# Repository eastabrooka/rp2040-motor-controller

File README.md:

# rp2040-motor-controller

## Note: This is a from the upstream Twisted-Fields/rp2040-motor-controller repo.

### Intro / First Level Why ? 

Well, I find this very interesting / funny. 

The previous EMFcamps I have attended, I have always tried to "Make something that moved humans". 

One of them was a giant DC Wheelchair powered Creeper, 

One of them was Wheelchair Gokart. 

The most recent was a Brushless Hoverboard Kart / Trike. 

In all of these cases, the motor controllers have let me down. 

So this is my current working directory for making my own "Flavour" of Brushless Motor Controller.

### Second Level Why ? 

Well, Brushless motor controllers are Expensive. Theres things like the VESC, ODrive and the cheap red 300W Aliexpress controllers. 

The Ali Express controlers I have had go bang. 

The ODrive controllers are *Way* too expensive, and now, sadly, closed source. (Little bit salty about that)

Honestly, the smart move would probably be : Just buy Aliexpress cloned odrive boards. 
But then I dont learn anything. 

Anyway, All the changes here are under the same CERN Permissive as upstream. 

*Our dream is that you will fab your own boards, make changes, and share your work - giving this design life beyond our efforts.* - So I hope this plays nice with that. 

More info to come when I start hacking about a bit more.

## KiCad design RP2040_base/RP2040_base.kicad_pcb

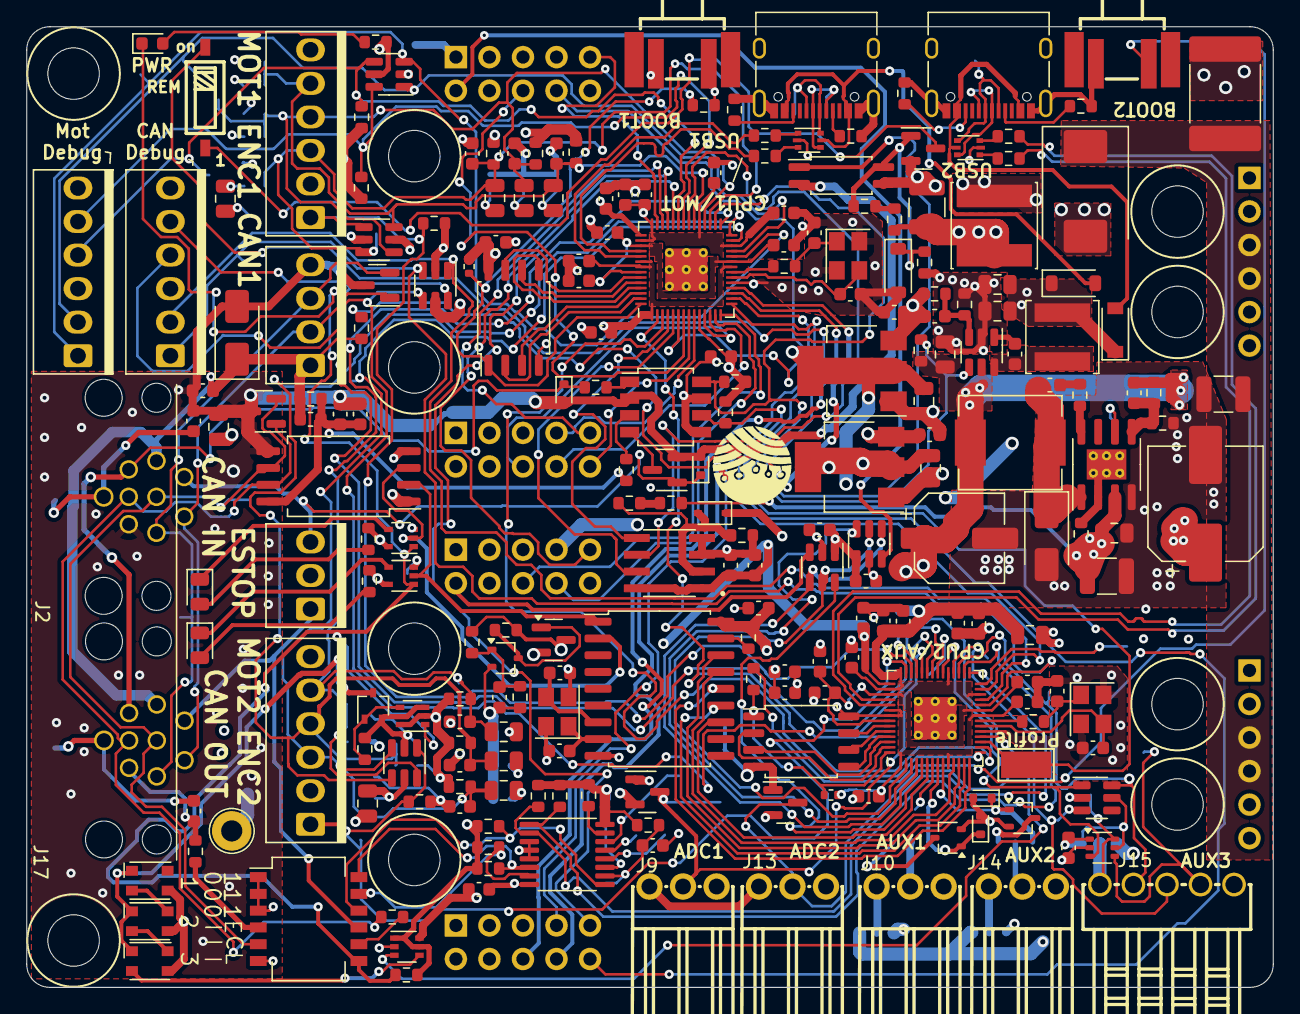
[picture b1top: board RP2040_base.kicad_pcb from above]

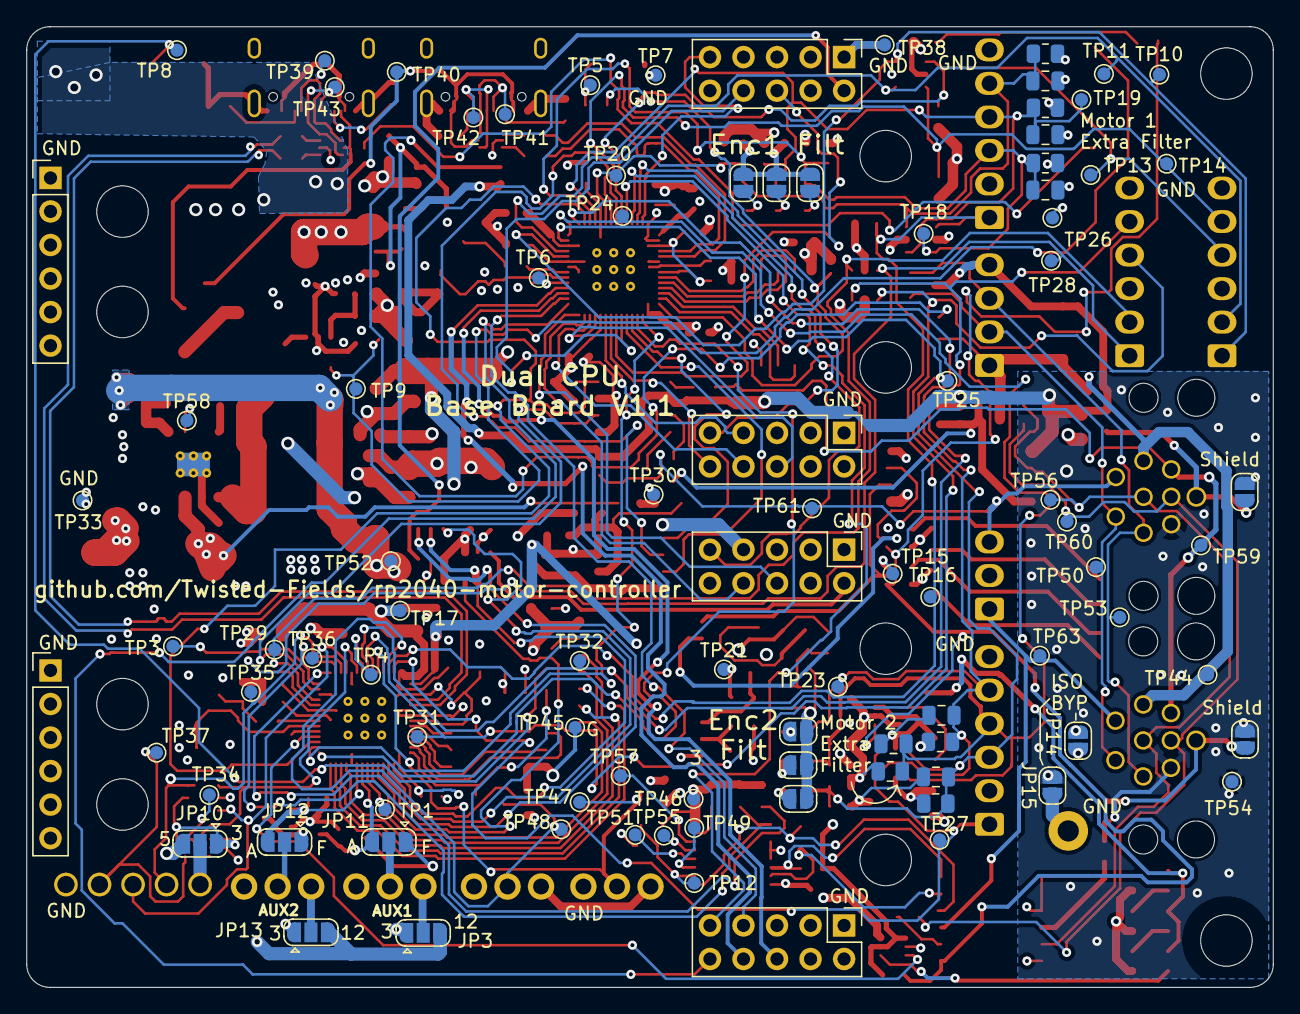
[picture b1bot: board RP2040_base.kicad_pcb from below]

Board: 4 copper layers, 94.4 x 72.8 mm, 315 parts (87 on the bottom side), 186 nets.

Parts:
C1, C8: 4.7uF 35V; C_0603_1608Metric
C2, C3, C111: 4.7uF 100V; C_1210_3225Metric
C4, C21, C22, C30, C31, C33, C36, C37, C38, C39, C40, C41, C43, C44, C45, C46, C47, C48, C49, C50, C51, C52, C55, C56, C67, C114, C119: 100n; C_0603_1608Metric
C5, C6, C7, C9, C10, C11: C_0805_2012Metric
C12, C13, C24, C29, C86, C110: 10u; C_0805_2012Metric
C14: 10uF 25v; C_0603_1608Metric
C15: 2.2u; C_0603_1608Metric
C18, C20, C32, C34, C35, C53, C54, C121, C122, C123, C124: 1u; C_0603_1608Metric
C19, C27, C28, C42: 20p; C_0603_1608Metric
C23, C60, C61, C62, C63, C64, C113: 47p; C_0603_1608Metric
C57, C58: 18p; C_0603_1608Metric
C87, C88, C89, C90, C91, C92: 22nF; C_0805_2012Metric
C94, C96: 22uF 25V; C_0805_2012Metric
C95: 47uF 10v; C_0805_2012Metric
C97: 22pF; C_0603_1608Metric
C98: 22nF; C_0603_1608Metric
C112: 100nF 100V; C_0805_2012Metric
C115: 220uF 25V; CP_Elec_6.3x7.7
C120: 47uF 63V solid; CP_Elec_8x10.5
D1, D40: ESDCAN24-2BLY; SOT-23
D3: TVS 5V; D_SMA
D4: SMAJ51A; D_SMC
D27: SS310; D_SMA
D28, D29, D30, D32: TVS 3.3V; D_SOD-523
D31: 1N4148WS; D_SOD-323
D33, D34, D35: WS2812B; LED_WS2812_3528_3.5x2.8mm_P1.5mm
D36, D44: BAT54S; SOT-23
D37, D43: B5819W SL; D_SOD-123
D38: LED_GREEN; LED_0805_2012Metric
D39: LED_YELLOW; LED_0805_2012Metric
D41: LED_RED; LED_0603_1608Metric
D45: 10V Zener; D_SOD-123
F1: 60V 1.5A hold polyfuse; Fuse_2920_7451Metric
FB2: 1.6Ω ±25% 1kΩ@100MHz; L_0603_1608Metric
H3, H4: MountingHole; MountingHole_3.9mm_Plastite_#6
J1: CPU1 USB; USB_C_Receptacle_XKB_U262-16XN-4BVC11
J2: CAN Input; M12A-08PFFR
J3: Encoder 1; Ckmtw-W-2510S06P_1x06_P2.54mm_Vertical
J4: Encoder 2; Ckmtw-W-2510S06P_1x06_P2.54mm_Vertical
J5, J12: Conn_01x06; Ckmtw-W-2510S06P_1x06_P2.54mm_Vertical
J6: CPU2 USB; USB_C_Receptacle_XKB_U262-16XN-4BVC11
J8: Estop Conn; BOOMELE-2510-3A_1x03_P2.54mm_Vertical
J9: ADC AUX 1; CONN-TH_3P-P2.54_HCTL_HC-2510-3AW
J10: AUX GPIO 1; CONN-TH_3P-P2.54_HCTL_HC-2510-3AW
J11: CAN2 PLUG; PINREX-744-81-04TW00 _1x04_P2.54mm_Vertical
J13: ADC AUX 2; CONN-TH_3P-P2.54_HCTL_HC-2510-3AW
J14: AUX GPIO 2; CONN-TH_3P-P2.54_HCTL_HC-2510-3AW
J15: AUX Encoder; CONN-TH_5P-P2.54_HCTL_HC-2510-5AW
J17: CAN Output; M12A-08PFFR
JP1, JP2, JP4, JP5, JP6, JP7, JP8, JP9, JP14, JP15: SolderJumper_2_Open; SolderJumper-2_P1.3mm_Open_RoundedPad1.0x1.5mm
JP3, JP10, JP11, JP12, JP13: SolderJumper_3_Open; SolderJumper-3_P1.3mm_Open_RoundedPad1.0x1.5mm
L1: 68uH 1A; L_Sunlord_SWPA6045S
L2: 10uH; L_Sunlord_SWPA5040S
L3: 47uH; L_Chilisin_BMRB00060612
Q1, Q2, Q11: AO7400-VB; SOT-323_SC-70
Q3: AO7401; SOT-23
Q4: LBSS139WT1G; SOT-323_SC-70
Q7, Q8: Q_NMOS_GSD; SOT-23
R1, R3, R4, R5, R6, R7: R_0805_2012Metric
R2, R23, R64: 50k 0.1%; R_0603_1608Metric
R8, R11, R12, R13, R14, R17, R18, R19, R53, R54, R55, R56, R57, R58, R72, R74, R79, R137, R138: 10k; R_0603_1608Metric
R9, R48, R75, R100: 120R; R_0603_1608Metric
R10: 510R; R_0603_1608Metric
R15: 110k 0.1%; R_0603_1608Metric
R16: 15k 0.1%; R_0603_1608Metric
R20, R21: 47k; R_0603_1608Metric
R22: 500k; R_0603_1608Metric
R40, R43, R44, R46, R49, R62, R63, R76: 5.1k; R_0603_1608Metric
R41, R47, R52, R66: 1.1k; R_0603_1608Metric
R42, R51: DNS; R_0402_1005Metric
R60, R61, R67, R70, R71: 27R; R_0603_1608Metric
R65: 5.1k 0.1%; R_0603_1608Metric
R68: 56R; R_0603_1608Metric
R77: 82R; R_0603_1608Metric
R95: 30mΩ 5%; R_0603_1608Metric
R96: 300k; R_0603_1608Metric
R97: 21.5k; R_0603_1608Metric
R98: 10Ω; R_0603_1608Metric
R99: 10.2R; R_0603_1608Metric
R103, R106: 100k; R_0603_1608Metric
SW1, SW5: KT11B2SAM34LFS; KEY-SMD_KT11B2SAM34LFS
SW3: CONFIG SWITCH; SW_DIP_SPSTx06_Slide_KingTek_DSHP06TS_W7.62mm_P1.27mm
SW4: SW_DIP_x01; SW-SMD_DSHP01TSGER
TP1, TP3, TP4, TP5, TP6, TP7, TP8, TP9, TP10, TP11, TP12, TP13, TP14, TP15, TP16, TP17, TP18, TP19, TP20, TP21, TP23, TP24, TP25, TP26, TP27, TP28, TP29, TP30, TP31, TP32, TP33, TP34, TP35, TP36, TP37, TP38, TP39, TP40, TP41, TP42, TP43, TP44, TP45, TP46, TP47, TP48, TP49, TP50, TP51, TP52, TP53, TP54, TP55, TP56, TP57, TP58, TP59, TP60, TP61, TP63: TestPoint; TestPoint_Pad_D1.0mm
TP2: TestPoint; TestPoint_Loop_D2.60mm_Drill1.6mm_Beaded
TP22: TestPoint; TestPoint_Keystone_5019_Minature
U1, U2: driver_module
U3, U29, U30, U31, U43: USBLC6-4SC6; SOT-23-6
U4, U10: TXS0101DCKR; SOT-363_SC-70-6
U6, U23, U25: SN74LVC1G07QDCKTQ1; SOT-353_SC-70-5
U9, U26: ADC081S021CISD/NOPB; SOT-23-6
U11, U32: TLV1117LV33DCYR; SOT-223-3_TabPin2
U12, U13: W25Q128JVSIQ; SOIC-8_5.23x5.23mm_P1.27mm
U15, U19: RP2040; RP2040-QFN-56
U16: SOP-4_4.4x2.6mm_P1.27mm
U17: CA-IS3052G; SOIC-8_7.5x5.85mm_P1.27mm
U18: MCP2515-xSO; SOIC-18W_7.5x11.6mm_P1.27mm
U22: ADS7822U; SOIC127P599X175-8N
U24: MT2492; SOT-23-6
U27, U28: USBLC6-2P6; SOT-666
U33: TX4139; SOIC-8-1EP_3.9x4.9mm_P1.27mm_EP2.29x3mm_ThermalVias
U34: LTV-208; SSOP-8_3.91x5.84x3.18mm_P1.27mm
U35: PCA9557PWR; TSSOP-16_4.4x5mm_P0.65mm
Y1, Y2: 12MHz; Crystal_SMD_3225-4Pin_3.2x2.5mm
Y3: 16MHz; Crystal_SMD_3225-4Pin_3.2x2.5mm

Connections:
+1V1: C30.1, C31.1, C32.1, U15.23 (DVDD), U15.45 (VREG_VOUT), U15.50 (DVDD)
+3.3VA: C18.2, C20.2, C22.1, C24.1, C35.2, C41.1, C52.1, D31.1 (K), D36.2 (K), D44.2 (K), J9.1, J13.1, U1.7 (+3V3), U2.7 (+3V3), U9.1 (VA), U11.2 (VO), U15.43 (ADC_AVDD), U19.43 (ADC_AVDD), U22.1 (VREF), U22.8 (+VCC), U26.1 (VA)
+3V3: C4.1, C12.2, C13.2, C21.1, C29.1, C33.1, C34.1, C36.1, C37.1, C38.1, C39.1, C40.1, C43.1, C46.1, C47.1, C48.1, C49.1, C50.1, C51.1, C54.1, C56.2, C67.1, C110.1, J3.2, J4.2, J5.3, J12.3, JP3.1 (A), JP10.1 (A), JP13.1 (A), R1.1, R3.1, R4.1, R5.1, R6.1, R7.1, R11.1, R12.1, R13.1, R17.1, R18.1, R19.1, R23.1, R42.1, R49.1, R51.1, R53.1, R54.1, R55.1, R56.1, R57.1, R58.1, R62.1, R63.2, R67.1, R68.1, R72.2, R76.1, R77.1, R137.2, TP17.1, TP26.1, TP30.1, TP46.1, U3.5 (VBUS), U4.1 (VCCA), U4.5 (OE), U6.5 (VCC), U10.1 (VCCA), U10.5 (OE), U12.8 (VCC), U13.8 (VCC), U15.1 (IOVDD), U15.10 (IOVDD), U15.22 (IOVDD), U15.26 (RUN), U15.33 (IOVDD), U15.42 (IOVDD), U15.44 (VREG_IN), U15.48 (USB_VDD), U15.49 (IOVDD), U17.1 (VCC1), U18.18 (VDD), U19.1 (IOVDD), U19.10 (IOVDD), U19.22 (IOVDD), U19.26 (RUN), U19.33 (IOVDD), U19.42 (IOVDD), U19.44 (VREG_IN), U19.48 (USB_VDD), U19.49 (IOVDD), U23.5 (VCC), U25.2 (A), U25.5 (VCC), U29.5 (VBUS), U30.5 (VBUS), U31.5 (VBUS), U32.2 (VO), U35.16 (VDD), U43.5 (VBUS)
+5V: C95.2, C96.2, C97.1, C119.1, C121.1, C122.1, D33.3 (VDD), D34.3 (VDD), D35.3 (VDD), D37.1 (K), D43.1 (K), JP10.3 (B), JP14.1 (A), L2.2, R15.2, U10.6 (VCCB), U11.3 (VI), U32.3 (VI)
+5V_ISO: C8.2, D3.1 (A1), FB2.2, J2.7, J11.1, J17.7, JP14.2 (B), R99.2, R100.1, TP44.1
+5V_ISO_FILT: C1.2, C55.2, FB2.1, R48.1, R99.1, U17.8 (VCC2)
+12V: C94.1, C113.1, C115.1, JP3.3 (B), JP13.3 (B), L3.2, Q3.3 (D), R20.2, R21.2, R96.2, R106.1, TP52.1, U24.5 (IN)
/1V1_2: C44.1, C45.1, C53.1, U19.23 (DVDD), U19.45 (VREG_VOUT), U19.50 (DVDD)
/5V_EN: R106.2, SW4.2, TP9.1, U24.4 (EN)
/12V_switched: Q3.2 (S), U1.5 (+12V), U2.5 (+12V)
/ADC_AUX1: D44.3 (COM), J9.2, TP47.1, U19.38 (GPIO26_ADC0)
/ADC_AUX2: D36.3 (COM), J13.2, TP48.1, U19.39 (GPIO27_ADC1)
/ADC_CLK: U9.4 (SCLK), U19.4 (GPIO2), U26.4 (SCLK)
/ADC_CS1: U9.6 (~CS), U19.3 (GPIO1)
/ADC_CS2: U19.5 (GPIO3), U26.6 (~CS)
/ADC_DATA: U9.5 (SDATA), U19.2 (GPIO0), U26.5 (SDATA)
/AUX1: D30.1 (A1), JP11.3 (B), Q1.1 (G), U19.8 (GPIO6)
/AUX2: D29.1 (A1), JP12.3 (B), Q2.1 (G), U19.9 (GPIO7)
/AUX3_CSn: J15.3, TP36.1, U19.32 (GPIO21), U31.3 (I/O2)
/AUX3_RX: J15.2, TP35.1, U19.31 (GPIO20), U31.6 (I/O4)
/AUX3_SCK: U4.3 (A), U19.34 (GPIO22), U31.1 (I/O1)
/AUX3_SCK_SHIFTED: J15.4, TP37.1, U4.4 (B)
/AUXV: J15.1, JP10.2 (C), TP34.1, U4.6 (VCCB)
/BS: R98.1, U33.8 (BS)
/Bridge_TH_1: U1.2 (Thermistor), U9.3 (VIN)
/Bridge_TH_2: U2.2 (Thermistor), U26.3 (VIN)
/CAN0_N: D1.2 (K), J2.8, J17.8, SW3.5, TP56.1, U17.6 (CANL)
/CAN0_P: D1.1 (K), J2.5, J17.5, R9.1, TP60.1, U17.7 (CANH)
/CAN1_N: D40.2 (K), J2.3, J11.3, J17.3, TP53.1
/CAN1_P: D40.1 (K), J2.2, J11.2, J17.2, TP50.1
/CANH0_P_JP: R9.2, SW3.8
/ENC1_CS: C7.2, C61.2, C88.1, J3.4, R3.2, R56.2, TP19.1, U15.32 (GPIO21), U29.4 (I/O3)
/ENC1_RX: C6.2, C62.2, C87.2, J3.3, R4.2, R58.2, TP18.1, U15.31 (GPIO20), U29.3 (I/O2)
/ENC1_SCK: C5.2, C60.2, C89.1, J3.5, R1.2, R54.2, TP20.1, U15.34 (GPIO22), U29.6 (I/O4)
/ENC2_CS: C11.2, C63.2, C91.2, J4.4, R6.2, R55.2, TP24.1, U15.28 (GPIO17), U30.4 (I/O3)
/ENC2_RX: C9.2, C64.2, C90.2, J4.3, R5.2, R57.2, TP25.1, U15.27 (GPIO16), U30.3 (I/O2)
/ENC2_SCK: C10.2, C23.2, C92.2, J4.5, R7.2, R53.2, TP23.1, U15.29 (GPIO18), U30.6 (I/O4)
/ESTOP: R76.2, TP22.1, U15.30 (GPIO19), U19.17 (GPIO14), U34.8
/ESTOP_SQUARE: D28.1 (A1), J2.6, J17.6, R75.1, TP59.1
/ESTOP_SWITCH_IN: D32.1 (A1), J2.1, J8.3, Q7.1 (G), TP61.1
/ESTOP_SWITCH_OUT: J8.1, J17.1, SW3.9, TP63.1
/ESTOP_SWITCH_STATUS: R49.2, U19.27 (GPIO16), U34.6
/FB: C113.2, R96.1, R97.2, U33.5 (FB)
/GPIO0: U15.2 (GPIO0), U19.16 (GPIO13)
/GPIO1: U15.3 (GPIO1), U19.15 (GPIO12)
/GPIO5_2: TP1.1, U19.7 (GPIO5)
/GPIO17_2: TP3.1, U19.28 (GPIO17)
/GPIO23: U15.35 (GPIO23), U22.6 (DOUT)
/GPIO23_2: TP4.1, U19.35 (GPIO23)
/GPIO24: J5.5, R62.2, TP14.1, U15.36 (GPIO24), U43.6 (I/O4)
/GPIO25: J5.4, R63.1, TP13.1, U15.37 (GPIO25), U43.4 (I/O3)
/ID1: R13.2, SW3.12, U35.6 (IO0)
/ID2: R12.2, SW3.11, U35.7 (IO1)
/ID3: R11.2, SW3.10, U35.9 (IO2)
/LED: U10.3 (A), U19.18 (GPIO15)
/QSPI_SCLK: U12.6 (CLK), U15.52 (QSPI_SCLK)
/QSPI_SCLK_2: U13.6 (CLK), U19.52 (QSPI_SCLK)
/QSPI_SD0: U12.5 (DI(IO0)), U15.53 (QSPI_SD0)
/QSPI_SD0_2: U13.5 (DI(IO0)), U19.53 (QSPI_SD0)
/QSPI_SD1: U12.2 (DO(IO1)), U15.55 (QSPI_SD1)
/QSPI_SD1_2: U13.2 (DO(IO1)), U19.55 (QSPI_SD1)
/QSPI_SD2: U12.3 (IO2), U15.54 (QSPI_SD2)
/QSPI_SD2_2: U13.3 (IO2), U19.54 (QSPI_SD2)
/QSPI_SD3: U12.7 (IO3), U15.51 (QSPI_SD3)
/QSPI_SD3_2: U13.7 (IO3), U19.51 (QSPI_SD3)
/QSPI_SS: R41.1, R42.2, U12.1 (~CS), U15.56 (QSPI_SS)
/QSPI_SS_2: R51.2, R66.1, U13.1 (~CS), U19.56 (QSPI_SS)
/RXD: U17.3 (RXD), U18.2 (RXCAN), U23.2 (A)
/RXI_2: J12.4, TP31.1, U3.4 (I/O3), U19.37 (GPIO25)
/SCL1: R18.2, U19.30 (GPIO19), U35.1 (SCL)
/SDA1: R19.2, U19.29 (GPIO18), U35.2 (SDA)
/SPI1_CSn_2: U18.16 (~CS), U19.12 (GPIO9)
/SPI1_INT: U18.12 (~INT), U19.6 (GPIO4)
/SPI1_RX_2: U18.15 (SO), U19.11 (GPIO8)
/SPI1_SCK_2: U18.13 (SCK), U19.13 (GPIO10)
/SPI1_TX_2: U18.14 (SI), U19.14 (GPIO11)
/SW: C114.1, D27.1 (K), L3.1, U33.1 (SW)
/SWCLK: J5.1, TP10.1, U15.24 (SWCLK), U43.3 (I/O2)
/SWCLK_2: J12.1, TP28.1, U3.3 (I/O2), U19.24 (SWCLK)
/SWD: J5.2, TP11.1, U15.25 (SWD), U43.1 (I/O1)
/SWD_2: J12.2, TP29.1, U3.1 (I/O1), U19.25 (SWD)
/TH_MOTOR1: J3.1, R74.1, TP16.1, U19.40 (GPIO28_ADC2), U29.1 (I/O1)
/TH_MOTOR2: J4.1, R79.1, TP27.1, U19.41 (GPIO29_ADC3), U30.1 (I/O1)
/TXD: U6.2 (A), U17.2 (TXD), U18.1 (TXCAN)
/TXO_2: J12.5, TP32.1, U3.6 (I/O4), U19.36 (GPIO24)
/USB_D+: J1.A6 (D+), J1.B6 (D+), TP41.1, U27.6 (I/O1)
/USB_D-: J1.A7 (D-), J1.B7 (D-), TP42.1, U27.4 (I/O2)
/USB_DN: R61.2, U15.46 (USB_DM)
/USB_DN_2: R71.2, U19.46 (USB_DM)
/USB_DP: R60.2, U15.47 (USB_DP)
/USB_DP_2: R70.2, U19.47 (USB_DP)
/USB_D_2+: J6.A6 (D+), J6.B6 (D+), TP43.1, U28.6 (I/O1)
/USB_D_2-: J6.A7 (D-), J6.B7 (D-), TP39.1, U28.4 (I/O2)
/VDC_CLK: U15.5 (GPIO3), U22.7 (DCLK)
/VDC_CS: U15.4 (GPIO2), U22.5 (~CS/SHDN)
/VMOT_RAW: C2.1, D4.1 (A1), F1.1, U1.23 (VMOT), U1.24 (VMOT), U2.23 (VMOT), U2.24 (VMOT)
/WS2812_SINK: D33.1 (GND), D34.1 (GND), D35.1 (GND), Q11.3 (D)
//LED_EN: D41.1 (K), R17.2, SW3.7, U6.1 (/OE), U23.1 (/OE), U25.1 (/OE)
/~USB_BOOT_2: R66.2, SW5.4, TP8.1
/~USB_BOOT: R41.2, SW1.4, TP5.1
GND: C2.2, C3.2, C4.2, C5.1, C6.1, C7.1, C9.1, C10.1, C11.1, C12.1, C13.1, C14.1, C15.2, C18.1, C19.2, C20.1, C21.2, C22.2, C23.1, C24.2, C27.2, C28.2, C29.2, C30.2, C31.2, C32.2, C33.2, C34.2, C35.1, C36.2, C37.2, C38.2, C39.2, C40.2, C41.2, C42.2, C43.2, C44.2, C45.2, C46.2, C47.2, C48.2, C49.2, C50.2, C51.2, C52.2, C53.2, C54.2, C56.1, C57.2, C58.2, C60.1, C61.1, C62.1, C63.1, C64.1, C67.2, C86.2, C94.2, C95.1, C96.1, C110.2, C111.2, C112.2, C115.2, C119.2, C120.2, C121.2, C122.2, D4.2 (A2), D27.2 (A), D29.2 (A2), D30.2 (A2), D36.1 (A), D44.1 (A), D45.2 (A), J1.A1 (GND), J1.A12 (GND), J1.B1 (GND), J1.B12 (GND), J1.S1 (SHIELD), J3.6, J4.6, J5.6, J6.A1 (GND), J6.A12 (GND), J6.B1 (GND), J6.B12 (GND), J6.S1 (SHIELD), J9.3, J10.3, J12.6, J13.3, J14.3, J15.5, JP1.1 (A), JP2.1 (A), JP4.1 (A), JP5.1 (A), JP8.1 (A), JP9.1 (A), JP15.1 (A), Q1.2 (S), Q2.2 (S), Q4.2 (S), Q8.2 (S), Q11.2 (S), R16.2, R22.1, R40.1, R43.1, R44.2, R46.2, R65.2, R74.2, R79.2, R97.1, R103.2, R138.2, SW1.2, SW3.1, SW3.2, SW3.3, SW3.6, SW5.2, TP2.1, TP6.1, TP7.1, TP15.1, TP21.1, TP33.1, TP38.1, TP45.1, U1.1 (GND), U1.11 (GND), U1.21 (GND), U1.22 (GND), U1.25 (GND), U1.26 (GND), U2.1 (GND), U2.11 (GND), U2.21 (GND), U2.22 (GND), U2.25 (GND), U2.26 (GND), U3.2 (GND), U4.2 (GND), U6.3 (GND), U9.2 (GND), U10.2 (GND), U11.1 (GND), U12.4 (GND), U13.4 (GND), U15.19 (TESTEN), U15.57 (GND), U16.3, U17.4 (GND1), U18.9 (VSS), U19.19 (TESTEN), U19.57 (GND), U22.3 (IN-), U22.4 (GND), U23.3 (GND), U24.2 (GND), U25.3 (GND), U26.2 (GND), U27.2 (GND), U28.2 (GND), U29.2 (GND), U30.2 (GND), U31.2 (GND), U32.1 (GND), U33.4 (GND), U34.5, U34.7, U35.3 (A0), U35.4 (A1), U35.5 (A2), U35.8 (VSS), U43.2 (GND), Y1.2, Y1.4, Y2.2, Y2.4, Y3.2, Y3.4
GND_ISO: C1.1, C8.1, C55.1, C86.1, C123.2, C124.2, D1.3 (A), D3.2 (A2), D28.2 (A2), D32.2 (A2), D40.3 (A), J2.4, J11.4, J17.4, JP6.1 (A), JP7.1 (A), JP15.2 (B), Q7.2 (S), R10.2, TP54.1, U16.2, U17.5 (GND2), U34.2
M1A_PWM_H: U1.16 (PWM_A_H), U15.11 (GPIO8)
M1A_PWM_L\: U1.18 (PWM_A_L\), U15.12 (GPIO9)
M1A_SENSE: U1.19 (SENSE_A), U15.40 (GPIO28_ADC2)
M1B_PWM_H: U1.20 (PWM_B_H), U15.8 (GPIO6)
M1B_PWM_L\: U1.17 (PWM_B_L\), U15.9 (GPIO7)
M1C_PWM_H: U1.8 (PWM_C_H), U15.6 (GPIO4)
M1C_PWM_L\: U1.6 (PWM_C_L\), U15.7 (GPIO5)
M1C_SENSE: U1.9 (SENSE_C), U15.41 (GPIO29_ADC3)
M2A_PWM_H: U2.16 (PWM_A_H), U15.17 (GPIO14)
M2A_PWM_L\: U2.18 (PWM_A_L\), U15.18 (GPIO15)
M2A_SENSE: U2.19 (SENSE_A), U15.38 (GPIO26_ADC0)
M2B_PWM_H: U2.20 (PWM_B_H), U15.15 (GPIO12)
M2B_PWM_L\: U2.17 (PWM_B_L\), U15.16 (GPIO13)
M2C_PWM_H: U2.8 (PWM_C_H), U15.13 (GPIO10)
M2C_PWM_L\: U2.6 (PWM_C_L\), U15.14 (GPIO11)
M2C_SENSE: U2.9 (SENSE_C), U15.39 (GPIO27_ADC1)
unnamed: C28.1, R52.2, Y1.1
unnamed: C42.1, R47.2, Y2.1
unnamed: C114.2, R98.2
unnamed: D31.2 (A), R64.2, R65.1, U22.2 (IN+)
unnamed: D33.2 (DIN), U10.4 (B)
unnamed: D33.4 (DOUT), D34.2 (DIN)
unnamed: D34.4 (DOUT), D35.2 (DIN)
unnamed: D38.2 (A), R67.2
unnamed: D38.1 (K), U6.4 (Y)
unnamed: D39.2 (A), R68.2
unnamed: D39.1 (K), U23.4 (Y)
unnamed: D41.2 (A), R77.2
unnamed: D45.1 (K), Q8.1 (G), R8.2, R103.1, U16.4
unnamed: F1.2, L1.1
unnamed: J1.A5 (CC1), R43.2
unnamed: J1.B5 (CC2), R44.1
unnamed: J6.A5 (CC1), R40.2
unnamed: J6.B5 (CC2), R46.1
unnamed: J10.1, JP3.2 (C)
unnamed: J10.2, JP11.2 (C)
unnamed: J14.1, JP13.2 (C)
unnamed: J14.2, JP12.2 (C)
unnamed: C92.1, JP1.2 (B)
unnamed: C89.2, JP2.2 (B)
unnamed: C90.1, JP4.2 (B)
unnamed: C91.1, JP5.2 (B)
unnamed: C123.1, J17.9, JP6.2 (B)
unnamed: C124.1, J2.9, JP7.2 (B)
unnamed: C88.2, JP8.2 (B)
unnamed: C87.1, JP9.2 (B)
unnamed: JP11.1 (A), Q1.3 (D)
unnamed: JP12.1 (A), Q2.3 (D)
unnamed: Q3.1 (G), Q4.3 (D), R20.1
unnamed: C14.2, Q4.1 (G), R21.1, R22.2
unnamed: Q7.3 (D), U34.4
unnamed: Q8.3 (D), SW4.1
unnamed: Q11.1 (G), R138.1, U25.4 (Y)
unnamed: R2.2, R64.1
unnamed: R10.1, SW3.4
unnamed: R8.1, R14.2
unnamed: R48.2, U34.3
unnamed: R60.1, U27.1 (I/O1)
unnamed: R61.1, U27.3 (I/O2)
unnamed: R70.1, U28.1 (I/O1)
unnamed: R71.1, U28.3 (I/O2)
unnamed: R75.2, U34.1
unnamed: R95.1, U33.2 (ILIM), U33.9 (ILIM)
unnamed: R100.2, U16.1
unnamed: C27.1, U15.20 (XIN), Y1.3
unnamed: R52.1, U15.21 (XOUT)
unnamed: C58.1, U18.8 (OSC1), Y3.1
unnamed: C57.1, U18.7 (OSC2), Y3.3
unnamed: R72.1, U18.17 (~RESET)
unnamed: C19.1, U19.20 (XIN), Y2.3
unnamed: R47.1, U19.21 (XOUT)
unnamed: C98.1, U24.1 (BS)
unnamed: C97.2, R15.1, R16.1, U24.3 (FB)
unnamed: C98.2, L2.1, U24.6 (SW)
unnamed: TP58.1, U33.6 (EN)
unnamed: C15.1, R23.2, TP12.1, U35.10 (IO3)
unnamed: TP49.1, U35.11 (IO4)
unnamed: TP51.1, U35.12 (IO5)
unnamed: TP55.1, U35.13 (IO6)
unnamed: TP57.1, U35.14 (IO7)
unnamed: R137.1, U35.15 (~RESET)
VBUS: D37.2 (A), J6.A4 (VBUS), J6.A9 (VBUS), J6.B4 (VBUS), J6.B9 (VBUS), U28.5 (VBUS)
VBUS2: D43.2 (A), J1.A4 (VBUS), J1.A9 (VBUS), J1.B4 (VBUS), J1.B9 (VBUS), TP40.1, U27.5 (VBUS)
VMOT: C3.1, C111.1, C112.1, C120.1, L1.2, R2.1, R14.1, R95.2, U33.3 (VIN)

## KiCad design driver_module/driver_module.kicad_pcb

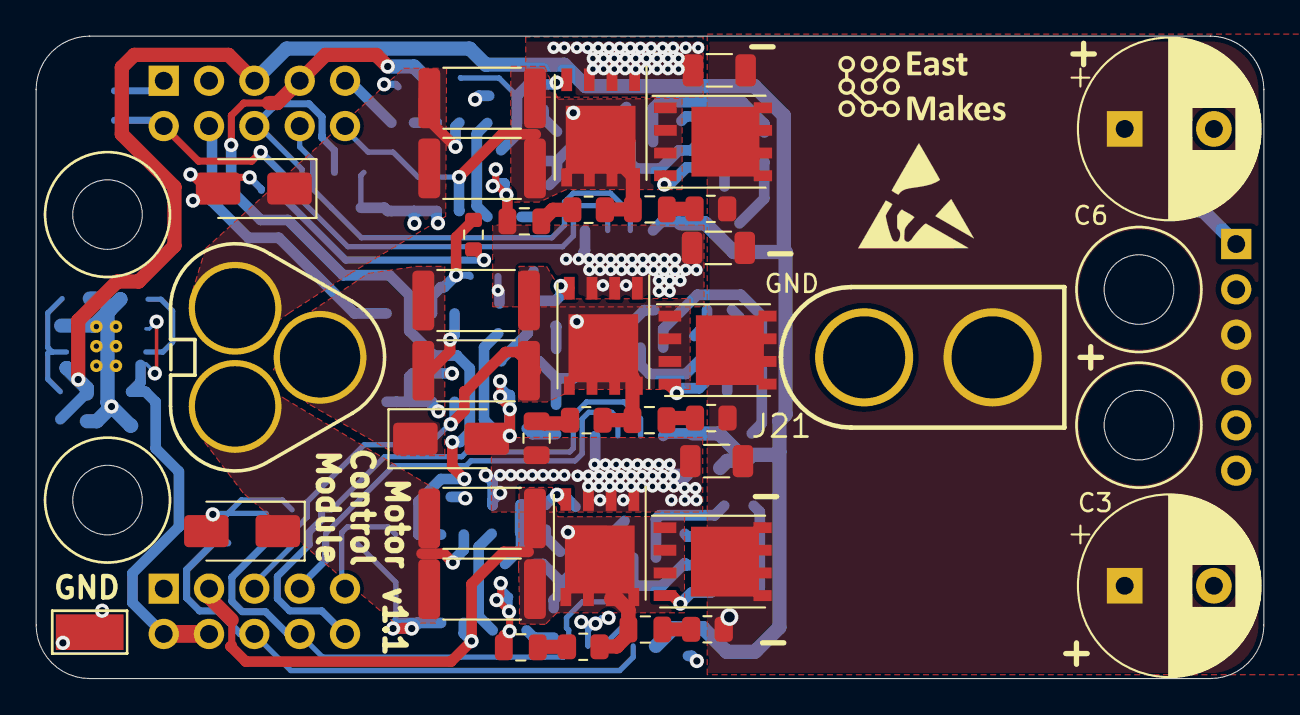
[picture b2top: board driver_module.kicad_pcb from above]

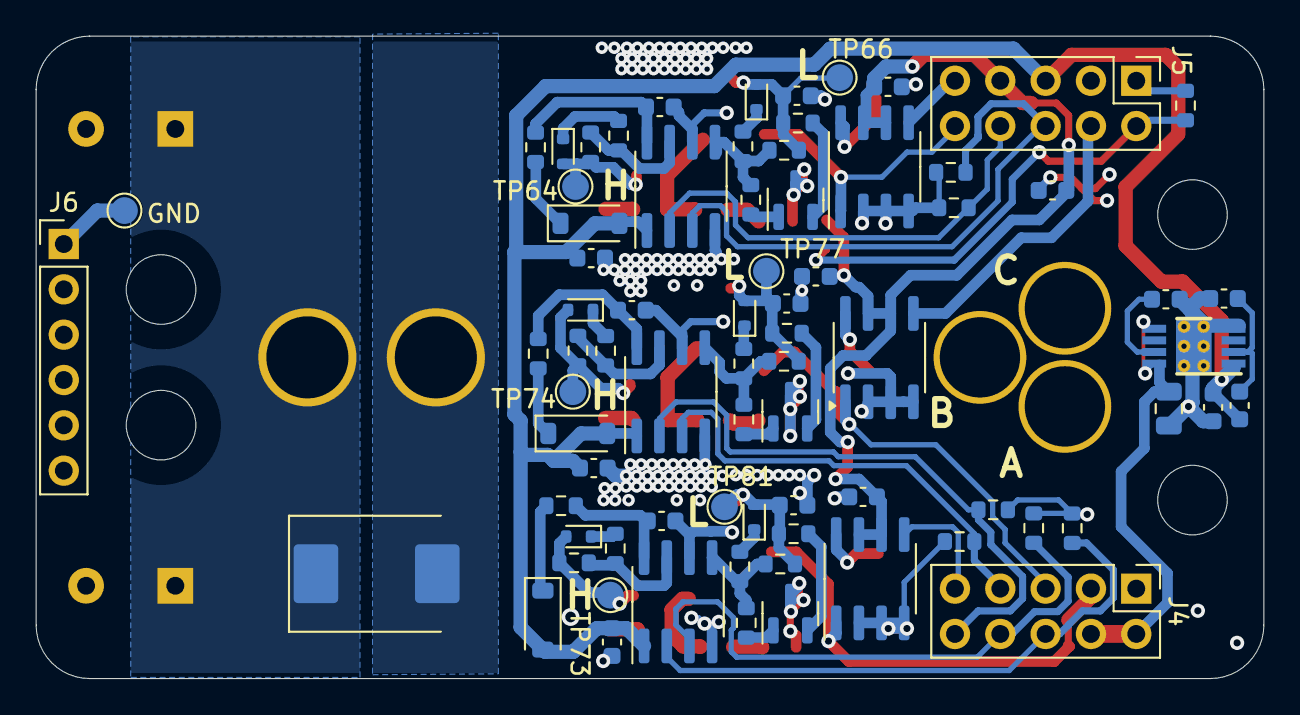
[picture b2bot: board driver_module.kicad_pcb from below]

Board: 4 copper layers, 68.8 x 36.0 mm, 116 parts (76 on the bottom side), 58 nets.

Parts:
AH2: MOSFETSO-8; PowerPAK_SO-8_123
AL2: MOSFETSO-8; PowerPAK_SO-8_123
BH2: MOSFETSO-8; PowerPAK_SO-8_123
BL2: MOSFETSO-8; PowerPAK_SO-8_123
C1, C66, C74: 100n; C_0603_1608Metric
C2, C8, C11, C15: 4.7uF 35V; C_0603_1608Metric
C3, C6: 220uF 63V solid; CP_Radial_D10.0mm_P5.00mm
C4: 1u; C_0603_1608Metric
C5: 2.2uF 100V; C_0805_2012Metric
C7, C9, C17, C25: DNP; C_0603_1608Metric
C13, C65, C70: 10uF 35v; C_0603_1608Metric
C77, C78, C79: 2.2uF 100V; C_1206_3216Metric
C101, C102, C103, C104, C105, C106: C; C_0805_2012Metric
CH2: MOSFETSO-8; PowerPAK_SO-8_123
CL2: MOSFETSO-8; PowerPAK_SO-8_123
D1: SMDJ51CA; D_SMC
D2, D7, D10: FR107; D_SOD-123
D5, D6, D14, D15, D16, D17: CDBU0130R-HF; D_SOD-523
D8, D9, D18: SMAJ51A; D_SMA
H1, H5, H6, H7: MountingHole; MountingHole_3.9mm_Plastite_#6
J4, J5: Conn_02x06_Odd_Even; PinHeader_2x05_P2.54mm_Vertical
J6: Conn_01x06; PinHeader_1x06_P2.54mm_Vertical
J19: Conn_01x03; MT60-F.G.Y
J21: Power Input; CONN-TH_XT60UPB-M
Q1, Q2, Q3: Q_PNP_BEC; SOT-23
R1, R3, R7, R8, R18, R22, R26, R30, R31: 0R; R_0603_1608Metric
R2, R9, R112: 100R; R_0603_1608Metric
R4, R5, R105, R109, R113, R114: 3mΩ; R_2512_6332Metric
R6, R10: R; C_0603_1608Metric
R23, R24, R25, R27, R28, R29, R32, R33, R36: 10.2R; R_0603_1608Metric
R45, R119, R120, R121, R122, R123, R124: 10k; R_0603_1608Metric
R86, R87, R88, R89, R90, R91: R; R_0805_2012Metric
TH1: Thermistor 10k; R_0603_1608Metric
TP64, TP66, TP73, TP74, TP77, TP81, TP94: TestPoint; TestPoint_Pad_D1.5mm_no_courtyard
TP71: TestPoint; TestPoint_Keystone_5019_Minature
U1, U21, U44: INA240A1D; SOIC-8_3.9x4.9mm_P1.27mm
U2, U5, U8: EG3113; SOIC-8_3.9x4.9mm_P1.27mm
U3: TPS7A1601DGNT; DGN0008C_N

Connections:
+3V3: C1.1, C4.1, C66.1, C74.1, J5.7, TH1.1, U1.6 (V+), U1.7 (REF1), U21.6 (V+), U21.7 (REF1), U44.6 (V+), U44.7 (REF1)
+12V: C2.2, C8.2, C11.2, C15.2, D2.2 (A), D7.2 (A), D10.2 (A), J5.5, R6.1, U2.1 (VCC), U3.1 (OUT), U5.1 (VCC), U8.1 (VCC)
/2AGH: AH2.2 (G), D17.2 (A), R33.2, TP73.1
/2AGL: AL2.2 (G), C17.2, D14.2 (A), R32.2, R36.2, TP81.1
/2BGH: BH2.2 (G), D15.2 (A), R24.2, TP74.1
/2BGL: BL2.2 (G), C25.2, D16.2 (A), R23.2, R25.2, TP77.1
/2CGH: CH2.2 (G), D6.2 (A), R28.2, TP64.1
/2CGL: C9.2, CL2.2 (G), D5.2 (A), R27.2, R29.2, TP66.1
/A_N: D18.1 (A1), J19.2, R105.2, R113.2, U21.8 (+)
/A_P: AH2.1 (S), AL2.3 (D), C70.1, C101.2, J4.3, R87.1, R105.1, R113.1, U8.6 (VS), U21.1 (-)
/B_N: D8.1 (A1), J19.3, R4.2, R5.2, U1.8 (+)
/B_P: BH2.1 (S), BL2.3 (D), C13.1, C106.2, J4.5, R4.1, R5.1, R90.1, U1.1 (-), U5.6 (VS)
/C_N: D9.1 (A1), J19.1, R109.2, R114.2, U44.8 (+)
/C_P: C65.1, C103.2, CH2.1 (S), CL2.3 (D), J5.10, R89.1, R109.1, R114.1, U2.6 (VS), U44.1 (-)
/TH1_SENSE: J5.2, R45.1, TH1.2
A_PWM_H: J4.6, R120.2, U8.2 (HIN)
A_PWM_L\: J4.8, R119.2, U8.3 (~LIN)
A_SENSE: J4.9, U21.5
B_PWM_H: J4.10, R121.2, U5.2 (HIN)
B_PWM_L\: J4.7, R122.2, U5.3 (~LIN)
B_SENSE: J5.4, U1.5
C_PWM_H: J5.8, R123.2, U2.2 (HIN)
C_PWM_L\: J5.6, R124.2, U2.3 (~LIN)
C_SENSE: J5.9, U44.5
GND: AL2.1 (S), BL2.1 (S), C1.2, C2.1, C3.2, C4.2, C5.2, C6.2, C7.1, C8.1, C9.1, C11.1, C15.1, C17.1, C25.1, C66.2, C74.2, C77.2, C78.2, C79.2, C102.2, C104.2, C105.2, CL2.1 (S), D1.2 (A2), D8.2 (A2), D9.2 (A2), D18.2 (A2), J4.1, J5.1, J5.3, J6.1, J6.2, J6.5, J6.6, J21.1, Q1.3 (C), Q2.3 (C), Q3.3 (C), R10.2, R45.2, R119.1, R120.1, R121.1, R122.1, R123.1, R124.1, TP71.1, TP94.1, U1.2 (GND), U1.3 (REF2), U1.4 (GND), U2.4 (COM), U3.4 (GND), U3.9 (PAD), U5.4 (COM), U8.4 (COM), U21.2 (GND), U21.3 (REF2), U21.4 (GND), U44.2 (GND), U44.3 (REF2), U44.4 (GND)
unnamed: C101.1, R86.2
unnamed: C102.1, R87.2
unnamed: C103.1, R88.2
unnamed: C104.1, R89.2
unnamed: C105.1, R90.2
unnamed: C106.1, R91.2
unnamed: D2.1 (K), R26.1
unnamed: D5.1 (K), R7.2
unnamed: D6.1 (K), R8.2
unnamed: D7.1 (K), R3.1
unnamed: D10.1 (K), R1.1
unnamed: D14.1 (K), R30.2
unnamed: D15.1 (K), R22.2
unnamed: D16.1 (K), R18.2
unnamed: D17.1 (K), R31.2
unnamed: Q1.1 (B), R2.2
unnamed: Q1.2 (E), R23.1
unnamed: Q2.1 (B), R9.2
unnamed: Q2.2 (E), R29.1
unnamed: Q3.1 (B), R112.2
unnamed: Q3.2 (E), R36.1
unnamed: R8.1, R28.1, U2.7 (HO)
unnamed: R7.1, R9.1, R27.1, U2.5 (LO)
unnamed: C65.2, R1.2, U2.8 (VB)
unnamed: C7.2, U3.7 (DELAY)
unnamed: R6.2, R10.1, U3.2 (FB)
unnamed: R22.1, R24.1, U5.7 (HO)
unnamed: R2.1, R18.1, R25.1, U5.5 (LO)
unnamed: C13.2, R26.2, U5.8 (VB)
unnamed: R31.1, R33.1, U8.7 (HO)
unnamed: R30.1, R32.1, R112.1, U8.5 (LO)
unnamed: C70.2, R3.2, U8.8 (VB)
VMOT: AH2.3 (D), BH2.3 (D), C3.1, C5.1, C6.1, C77.1, C78.1, C79.1, CH2.3 (D), D1.1 (A1), J4.2, J4.4, J6.3, J6.4, J21.2, R86.1, R88.1, R91.1, U3.5 (EN), U3.8 (IN)

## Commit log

2024-08-04 Update my own Readme file.
2024-08-04 Add in my *Private* Submodule, that keeps all my footprints.
    Still "OK" for Licencing, Anything that I use in the Schematic / PCB is encoded into the .sch / pcb files.
2024-08-04 Generate Gerbers for JLC for Motor Driver Board.
2024-08-04 Remove 2nd Motor Stuff.
2024-08-04 Make V1 Motor Board.
